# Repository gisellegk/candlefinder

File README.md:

# candlefinder
ROS candlefinder

Root folder should be a ROS workspace.

# Topics
## Candlefinder topics:

### start_bool
Published by: serial_node
Subscribed to by:
Message type: std_msgs::Bool

__msg.data__: Boolean value, "true" if the robot should start.

### drive_vector
Published by: control, teleop_robot (robot_teleop.cpp)
Subscribed to by: serial_node
Message type: geometry_msgs::Twist

__msg.angular.z__: The target angle for the robot to turn, in degrees. This is an absolute position relative to the base's start position.
__msg.linear.x__: The target speed for the robot, from 0 to 100.

### base_pose
Published by: serial_node
Subscribed to by: camera_scan_map_node (camera_scan_map.cpp)
Message Type: geometry_msgs::Twist

__msg.angular.z__: The current angle of the robot's drive base, in degrees. This is an absolute position relative to the base's start position.
__msg.linear.x__: The current speed for the robot, from 0 to 100.

### target_head_angle
Published by: navigation_node (navigation.cpp)
Subscribed to by: serial_node
Message Type: geometry_msgs::Quaternion

__msg.z__: The target angle for the robot's head to turn, in degrees. This is an absolute position relative to the head's start position.

### current_head_angle
Published by: serial_node
Subscribed to by: camera_scan_map_node (camera_scan_map.cpp)
Message Type: geometry_msgs::Quaternion

__msg.z__: The current angle of the robot's head, in degrees. This is an absolute position relative to the head's start position.

### camera_scan_map
Published by: camera_scan_map_node (camera_scan_map.cpp)
Subscribed to by: navigation_node (navigation.cpp)
Message Type: nav_msgs::OccupancyGrid

__msg.info__: A collection of useful information about the map, including its width, height, and resolution. See nav_msgs::MapMetaData.

__msg.data__: An array of integers representing the map surrounding the robot, indicating where the robot has already scanned with its camera.

- -1 = unexplored
- 1 = camera has seen here
- 100 = robot is here (currently gets overridden anyways)

### cost_map
Published by: cost_map_node (cost_map.cpp)
Subscribed to by: navigation_node (navigation.cpp)
Message Type: nav_msgs::OccupancyGrid

__msg.info__: A collection of useful information about the map, including its width, height, and resolution. See nav_msgs::MapMetaData.

__msg.data__: An array of integers representing the map surrounding the robot, except all wall obstacles have been inflated, indicating where the center of the robot should avoid in order to prevent collisions.

- -1 = unexplored
- 0 = mapped and unoccupied.
- 75 = buffer zone?
- 99 = inflated obstacle area
- 100 = obstacle from hector_map

### nav_map
Published by: navigation_node (navigation.cpp)
Subscribed to by: control
Message Type: nav_msgs::OccupancyGrid

__msg.info__: A collection of useful information about the map, including its width, height, and resolution. See nav_msgs::MapMetaData.

__msg.data__: An array of integers

- -1 = unexplored
- 0 = in current search window
- 50 = right-angle only path
- 100 = path to be followed

### navGoal
Published by:
Subscribed to by: navigation_node (navigation.cpp)
Message Type: geometry_msgs::Point

__msg.info__: Target for pathfinding algorithim. If set to -1,-1 it is ignored, otherwise, the algorithm trys to find a path to this specific point

### exploration_target_angle
Published by: navigation_node (navigation.cpp)
Subscribed to by: control
Message Type: std_msgs::Int16

__msg.data__: An integer representing the angle the robot should turn in order to drive to the nearest unexplored area. Range: 0 to 360, always positive.

### candle_loc
Published by: FLIR_node (FLIR_node.py)
Subscribed to by:
Message Type: geometry_msgs::Point

__msg.x__: The x-position of the flame in the camera's vision. -1 if none available.

__msg.y__: The y-position of the flame in the camera's vision. -1 if none available.

### extinguish
Published by:
Subscribed to by: serial_node
Message Type: std_msgs::Bool

__msg.data__: Boolean value, true if CO2 valve should be opened

## Hector topics:
### map
Subscribed to by: camera_scan_map_node (camera_scan_map.cpp), cost_map_node (cost_map.cpp)
Message Type: nav_msgs::OccupancyGrid

### slam_out_pose
Subscribed to by: camera_scan_map_node (camera_scan_map.cpp), navigation_node (navigation.cpp)
Message Type: geometry_msgs::PoseStamped

## Serial Reference:

read and write to serial port:
  /dev/ttyUSB1 (or adjust as needed)
  9600 baud

## Read and publish:
  start_bool:
    - g* for go
  base_pose
    - a* for angle
    - s* for speed
  current_head_angle
    - h* for head angle

## Process and Write to serial:
  drive_vector
    - a* for angle
    - s* for speed
  target_head_angle
    - h* for head angle
  extinguish
    - e* for extinguish flag

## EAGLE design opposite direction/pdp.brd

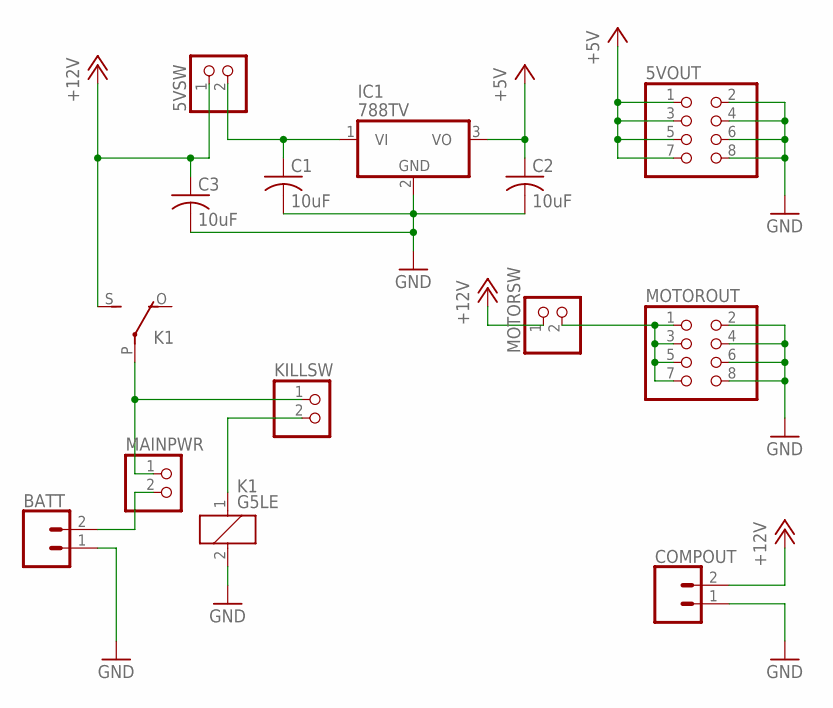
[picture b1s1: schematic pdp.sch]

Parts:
5VOUT: PINHD-2X4; 2X04
5VSW: PINHD-1X2; 1X02
BATT: CONN_025MM; SCREWTERMINAL-5MM-2
C1, C2, C3: 10uF; C0805
COMPOUT: CONN_025MM; SCREWTERMINAL-5MM-2
IC1: 788TV; TO220V
K1: G5LE
KILLSW: PINHD-1X2; 1X02
MAINPWR: PINHD-1X2; 1X02
MOTOROUT: PINHD-2X4; 2X04
MOTORSW: PINHD-1X2; 1X02

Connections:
+5V: 5VOUT.1, 5VOUT.3, 5VOUT.5, 5VOUT.7, C2.1, IC1.3 (VO)
+12V: 5VSW.1, C3.1, COMPOUT.2, K1.S, MOTORSW.1
GND: 5VOUT.2, 5VOUT.4, 5VOUT.6, 5VOUT.8, BATT.1, C1.2, C2.2, C3.2, COMPOUT.1, IC1.2 (GND), K1.2, MOTOROUT.2, MOTOROUT.4, MOTOROUT.6, MOTOROUT.8
unnamed: BATT.2, MAINPWR.2
unnamed: K1.P, KILLSW.1, MAINPWR.1
unnamed: K1.1, KILLSW.2
unnamed: 5VSW.2, C1.1, IC1.1 (VI)
unnamed: MOTOROUT.1, MOTOROUT.3, MOTOROUT.5, MOTOROUT.7, MOTORSW.2

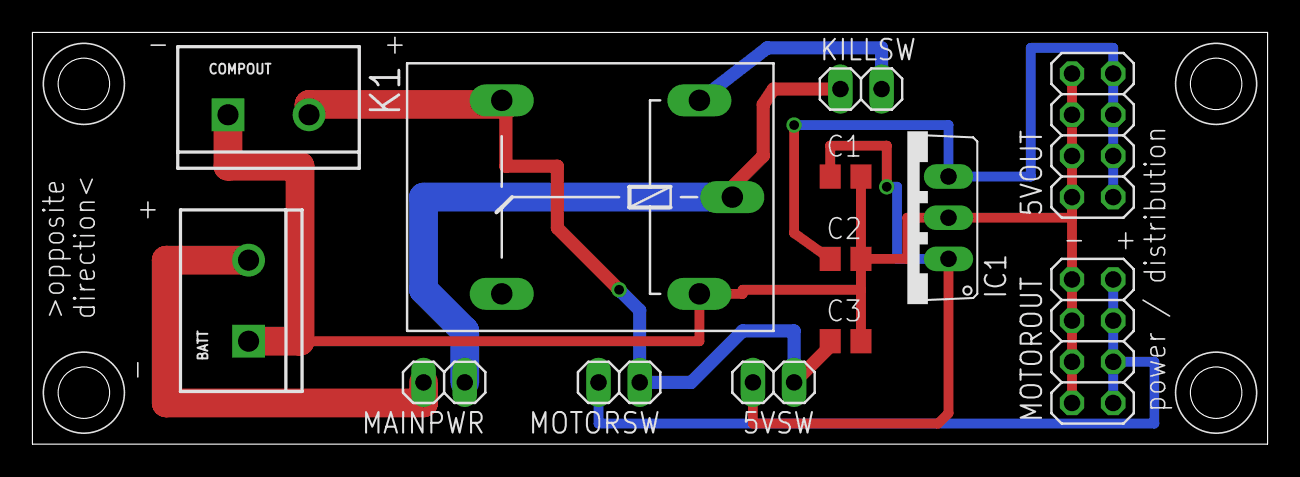
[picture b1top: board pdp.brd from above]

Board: 2 copper layers, 76.2 x 25.4 mm, 13 parts (0 on the bottom side), 8 nets.

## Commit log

2017-03-14 initial commit :)
2017-03-14 it compilessss
2017-03-16 example subscriber
2017-03-16 add driveduino
2017-03-17 add drive code
2017-03-17 add prints & homing function
2017-03-17 add stepperOff, compliling stuff, pull up resistor enabled for home switch
2017-03-17 add teleop code
2017-03-20 no idea....
2017-03-20 just listen on start_bool :)
2017-03-20 move motors in loop instead of callback
2017-03-27 i think this is just minor driving stuff that never got committed
2017-03-29 add barebones camera scan code
2017-03-29 ignored libraries in src folder
2017-03-29 add cmake and package stuff for compiling
2017-03-29 header files? what are those
2017-03-29 compiles now
2017-03-29 angle
2017-03-29 what are angles
2017-03-29 look at this TRIG
2017-03-29 what do you mean binary xor
2017-03-29 YAW?
2017-03-29 in rplidar_ros/launch/hectormapping.launch set use_tf_scan_transformation to false
2017-03-29 this maybe does the ray thing? set numRays to how many rays you want to do
2017-03-29 oh yeah make it stop at some radius
2017-03-30 the problem was radians. and rounding. and some other things
2017-03-30 some housekeeping & trying to make camera map persist
2017-03-30 add spinduino code :)
2017-03-30 change name of topics to be distinct
2017-03-30 documentationgit status!
2017-03-31 should do a 60 degree cone from the camera angle idk
2017-03-31 oh yeah header files exist
2017-03-31 take base angle into account
2017-03-31 tfw u forget semicolon
2017-03-31 print
2017-03-31 wrong angle whoops
2017-03-31 reverse angle
2017-03-31 try to draw a circle around the robot or something
2017-03-31 when in doubt ask stack overflow
2017-03-31 launch file
2017-03-31 I wonder if this breadth frist thing works
2017-03-31 cost map?
2017-03-31 compile pls
2017-03-31 nav!
2017-03-31 remove persistence
2017-03-31 change to cost_map
2017-04-01 see if this unborks it
2017-04-01 only nav <=50
2017-04-01 um idk. we did a bunch of little things and it works now
2017-04-01 find goal and draw line
2017-04-01 add spinduino test files
2017-04-01 navigation stops segfaulting i think
2017-04-01 it not workin so debug
2017-04-01 um maybe the right step count for a 103H546
2017-04-01 bloop
2017-04-01 updated angle math
2017-04-01 smart turning is smart. or something like that idk
2017-04-01 i cant type omfg
2017-04-01 revert cause we cant do maths
2017-04-01 ctrl+z
2017-04-01 update documentationoids
2017-04-01 added nav_map info
2017-04-01 pub an array
2017-04-01 typos
2017-04-01 path_plan
2017-04-01 oops
2017-04-01 add ir sensor stuff
2017-04-01 co2 valve stuff
2017-04-01 update doucmatnationoids
2017-04-01 add control node
2017-04-01 control progress
2017-04-01 flame case partially done
2017-04-01 compile time ig uess haha
2017-04-01 imsotired
2017-04-01 dlkajflksjd
2017-04-01 um start pls
2017-04-01 i just did someting but dont remember.. 2 tirerdrdddd
2017-04-01 add anotherfilter to threshold
2017-04-01 add more control code
2017-04-01 cakes
2017-04-01 um ffts
2017-04-02 no delay >_>
2017-04-02 misc
2017-04-02 less flickr
2017-04-02 wip control
2017-04-02 spin plz
2017-04-02 home better
2017-04-02 idk i think it works now
2017-04-02 turn wheelz plz
2017-04-02 dony forgot to read from the end
2017-04-02 should work now idk
2017-04-02 homes line up
2017-04-02 path finding progress
2017-04-02 vision data works haha
2017-04-02 center on camera
2017-04-02 add .sh file but it doesn't automatically run this yet
2017-04-07 processing pathfinding test:
2017-04-07 some comments
2017-04-07 added maze 2 and made minor changes
2018-01-22 hardware
2018-03-13 completed schematic for controller
2018-03-25 lmao what is this
2018-03-30 working uvc thing with thermal camera
2018-03-31 WORKING FLIR NODE
2018-03-31 WORKING FREAKING DRIVE TELE-OP
2018-03-31 moved controllerboard.ino
2018-03-31 circle cost map
2018-03-31 tweaked camera scan map
2018-04-01 idk, pathsmooooothing/
2018-04-01 almost there
2018-04-01 publish target angle on /target_vector
2018-04-01 updated FOV constant
2018-04-01 rotated flir image
2018-04-02 minor display tweaks and datatype fixes
2018-04-04 serial port spits out data
2018-04-04 added parsing for some more components...
2018-04-04 write serial comm, update documentation
2018-04-04 add serial library to gitignore
2018-04-04 remove chatter, add more publishy stuff to serial
2018-04-04 testing serial node. so far so good.
2018-04-05 WE FREAKING DRIVE AROUND
2018-04-05 it sort of does an angle thing
2018-04-06 explores whole maze and looks at everthing, but does not ever stop
2018-04-06 we stop when we find the candle, still should do something if there is no path
2018-04-07 idk lets not run into walls
2018-04-07 idk better pathfinding?
2018-04-07 hey, we are actually pretty fast
2018-04-07 wiggle on startup
2018-04-07 nav goal... this *shouldn't* break stuff
2018-04-07 candle centers
2018-04-08 well i hope this works lmao
2018-04-08 idk speed up robot
2018-04-08 attempt to approach candle
    tfw no ssh
2018-04-08 nav goal stuff
2018-04-08 i think this navgoal thing might work
2018-04-08 this compiles now
2018-04-08 WOOHOO CAN FIND THE CANDLE
2019-04-17 IDK THIS IS SOOO OLD
2019-04-17 get max col value from FLIR cam
2019-04-25 Heatmap works, so thats cool

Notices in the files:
parts and their libraries:
SparkFun-Connectors: Licensing: Creative Commons ShareAlike 4.0 International - https://creativecommons.org/licenses/by-sa/4.0
